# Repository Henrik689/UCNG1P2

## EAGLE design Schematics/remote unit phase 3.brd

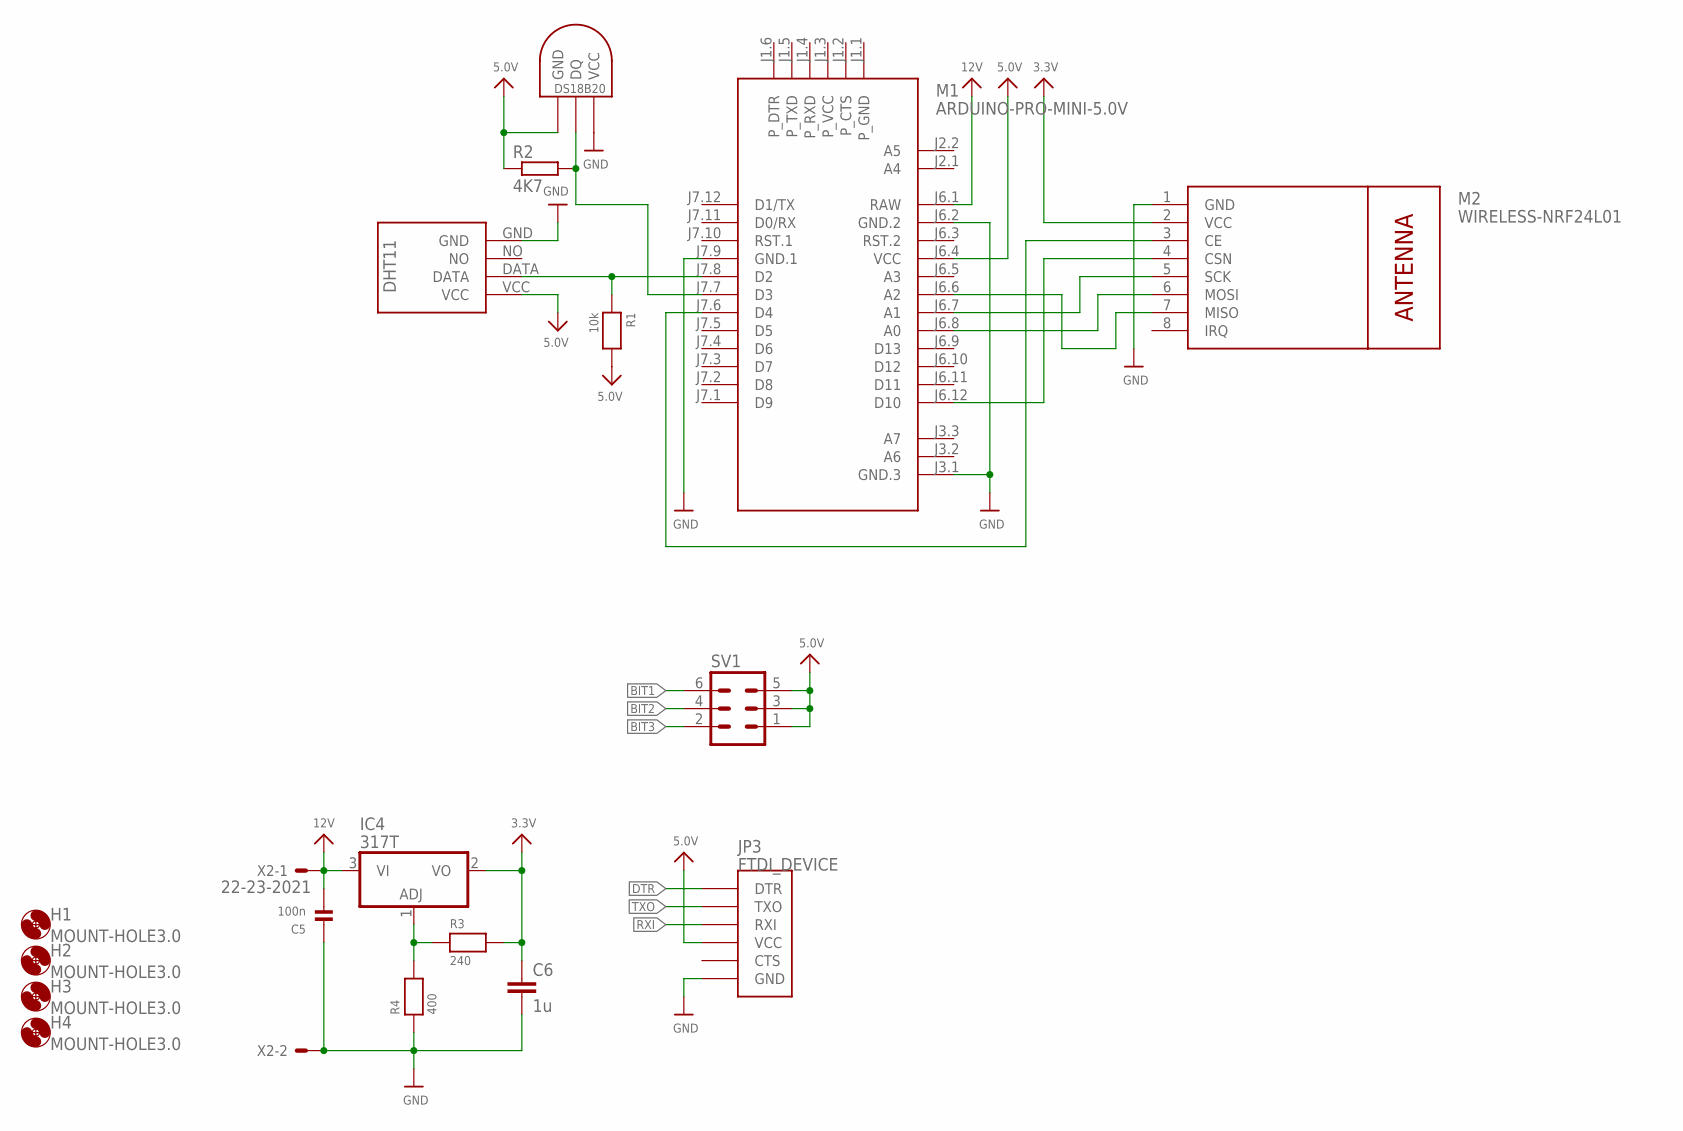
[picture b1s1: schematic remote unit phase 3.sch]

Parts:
C5: 100n; _0603
C6: 1u; C050-035X075
H1, H2, H3, H4: MOUNT-HOLE3.0; 3,0
IC4: 317T; TO220H
JP3: FTDI_DEVICE; FTDI_DEVICE_SIDE
M1: ARDUINO-PRO-MINI-5.0V; ARDUINO-PRO-MINI
M2: WIRELESS-NRF24L01
R1: 10k; _0603
R2: 4K7; 0204/5
R3: 240; _0603
R4: 400; _0603
SV1: MA03-2
U$6: DHT11
U$14: DS1820TO92; DS1820
X2: 22-23-2021

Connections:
3.3V: C6.1, IC4.2 (VO), M2.2 (VCC), R3.2
5.0V: JP3.P$4 (VCC), M1.J6.4 (VCC), R1.2, R2.1, SV1.1, SV1.3, SV1.5, U$6.VCC, U$14.GND
12V: C5.2, IC4.3 (VI), M1.J6.1 (RAW), X2.1
BIT1: SV1.6
BIT2: SV1.4
BIT3: SV1.2
CE: M1.J7.6 (D4), M2.3 (CE)
CSN: M1.J6.12 (D10), M2.4 (CSN)
DHT11: M1.J7.8 (D2), R1.1, U$6.DATA
DTR: JP3.P$1 (DTR)
GND: C5.1, C6.2, JP3.P$6 (GND), M1.J3.1 (GND.3), M1.J6.2 (GND.2), M1.J7.9 (GND.1), M2.1 (GND), R4.1, U$6.GND, U$14.VDD (VCC), X2.2
MISO: M1.J6.6 (A2), M2.7 (MISO)
MOSI: M1.J6.8 (A0), M2.6 (MOSI)
unnamed: IC4.1 (ADJ), R3.1, R4.2
RXI: JP3.P$3 (RXI)
SCK: M1.J6.7 (A1), M2.5 (SCK)
TEMP: M1.J7.7 (D3), R2.2, U$14.DQ
TXO: JP3.P$2 (TXO)

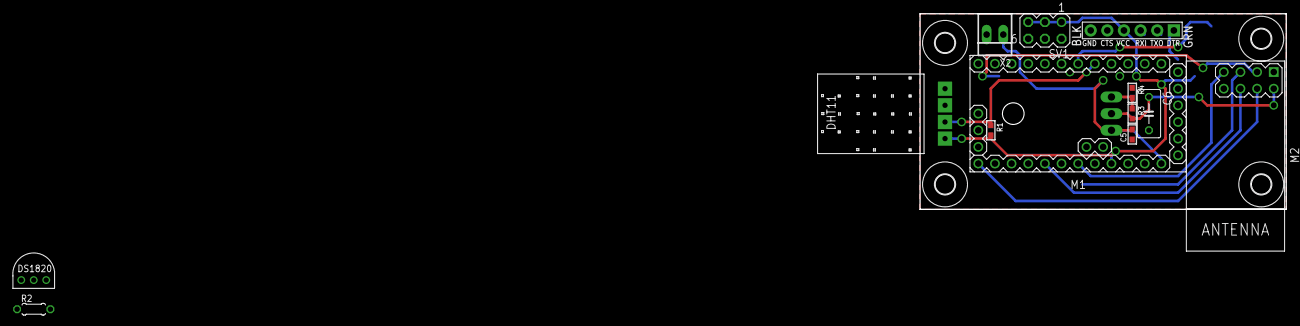
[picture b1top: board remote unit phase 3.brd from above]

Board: 2 copper layers, 55.9 x 29.8 mm, 18 parts (1 on the bottom side), 12 nets.

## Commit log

2016-01-04 added rapport for future editing
2016-01-04 Rod
    Har ændret enkelte ting introduktion
2016-01-04 Ændret forside til nyt projekt
2016-01-04 Ændringer i titlesheet og preface
2016-01-04 Ændringer i rapporten
    Rapporten er slavisk kørt igennem med ændringer
2016-01-04 tilføjet filer og ændret i master
    tilføjet sensor og accepttest
2016-01-04 ændring i master
2016-01-04 Removed ignored files
2016-01-04 sensor afsnit
    skrevet en smule på det
2016-01-04 Kravspecifikation
2016-01-04 ændret i sensor afsnit
2016-01-04 rettet kravspec
2016-01-04 sensor afsnit lavet tabel (ikke færdig)
2016-01-05 rettelser i kravsepc
2016-01-05 Introduktion til kravspec
2016-01-05 Kildehenvisning begyndt
2016-01-05 sensor afsnit
2016-01-05 tilføjet problemanalyse dokument
2016-01-05 hardware krav lavet
2016-01-05 TBD i hardware krav
2016-01-05 tilføjet 2 filer til problemanalyse
2016-01-05 Fixet tabel caption
2016-01-05 Enkelte stavefejl
2016-01-05 Billeder af fase 1-3
2016-01-05 indleding afsnit
2016-01-05 ændringer i master
2016-01-06 rettelse i hardware
2016-01-06 Hardware diagram indsat
2016-01-06 tilføjet krav til software afsnit
2016-01-06 Ændret i kravspec
2016-01-06 Software flowchart tilføjet
2016-01-06 Ændringer i software og master
2016-01-06 Intro til hardware samt fix af figure caption
2016-01-06 problemanalyse
2016-01-06 indledning redigeret
2016-01-06 fxnote test
2016-01-06 added fixme package
2016-01-07 FixMe notes tilføjet til alle sider
2016-01-07 tilføjet .lox og .nls til gitignore
2016-01-07 One Wire eksempel blibbiotek
2016-01-08 one wire filer
2016-01-11 tilføjet sensor afsnit
2016-01-11 Initimingfig
2016-01-11 ændring i sensor afsnit + tilføjet billeder
2016-01-11 Uploadet schematics
2016-01-11 Indsat subsection til schematic
2016-01-11 Schematics og billeder hertil
    Ikke helt færdig
2016-01-11 mikroprocessor startet
2016-01-12 litteraturliste
2016-01-12 ds18b20 tilføjet til litteraturliste
2016-01-12 software afsnit
2016-01-12 Fase1 software flowchart1
2016-01-12 mikroprocessor done
2016-01-12 mikroprocessor indsat billede
2016-01-12 rettelse i mikroprocessor
2016-01-12 Mikroprocessor_rettet
2016-01-13 rettelse af sensorafsnit, og sidste schematics
2016-01-13 Mikroprocessor_rettelse2
2016-01-13 microprocessor rettelse 3
2016-01-13 Rettelse af figurFase1software2
2016-01-13 hardware krav redigeret
2016-01-13 Rettelse af softwarestruktur
2016-01-13 Figur Fase1software2
2016-01-13 hardware introduktion lavet
2016-01-13 Onewire eksempel
2016-01-13 Software opdate
2016-01-13 Glossary ændret og hardware sensor påbegyndt
2016-01-13 Mikro update
2016-01-13 Problemanalysen update
2016-01-13 ds18b20 færdigt i hardware
2016-01-13 sensor redigeret i hardware
2016-01-13 Billeder til vandspild
2016-01-13 Tilføjet dht11 i hardware
2016-01-14 Figur update i PA
2016-01-14 Figur update PA
2016-01-14 Update PA
2016-01-14 rettet i sensor i hardware
2016-01-14 PA update
2016-01-14 flyttede videre udvikling over konklussion
2016-01-14 fxnote
2016-01-14 Update på indledningen
2016-01-14 Update indledning
2016-01-14 enkelte rettelser i software
2016-01-14 indsat tabel og pris i hardware samt redigeret i sensor tabel
2016-01-14 tal rettet i hardware tabel
2016-01-14 flyttede videre udvikling igen
2016-01-14 har fikset flowchart for fase 2
2016-01-15 tilføjet labet til fase 1 flowchart
2016-01-15 tilføjet label til fase 1 flowchart
2016-01-15 minor settings change and more work on rapport
2016-01-16 har fået skrevet om fase 2 og websiden samt ethernet
2016-01-16 hard- og software pris og tabel lavet
2016-01-16 BOM fjernet og redigeret pris hard- og software
2016-01-16 Fået skrevet det meste af afsnittet færdigt
    mangler at færdiggøre mesh afsnittet
2016-01-17 PA klar til gennemlæsning
2016-01-17 fortsat arbejde på videre udvikling
2016-01-17 Arkitektur og software beskrivelse
2016-01-18 sensor+one wire afsnit
2016-01-18 added .lox to git ignore
2016-01-18 removed accepttest
2016-01-18 opdateret grafer til vandspild
2016-01-18 konklusion
2016-01-18 Pris færdig - soft- og hardware
2016-01-18 Begrundelse for DHT11
2016-01-18 master + konklusion + perspektivering
2016-01-18 Konklussion + perspektivering
2016-01-18 fxnotes
2016-01-18 master
2016-01-18 master Porsborg har mærkelige fejl
2016-01-19 startet på rette processen
2016-01-19 master tidsplan
2016-01-20 Rettelser i mange filer, inkl en figur og .lox
2016-01-20 Forkortelser og små rettelser
2016-01-20 konklusion
    skrevet helt om
2016-01-20 Små rettelser
2016-01-20 har fikset listen med forkortelser
2016-01-20 Videreudvikling rettelser
2016-01-20 færdig med at tilføje forkortelser til glossary listen
2016-01-20 rettelser og milesten
2016-01-20 kravspek og hardware spek
2016-01-20 master - slettet user guide
2016-01-20 rettelser i software
2016-01-20 Gennemlæsning af hardware
2016-01-20 software DONE
2016-01-20 Software DONE igen....
2016-01-20 master ændret
2016-01-20 Oversat lister til dansk
2016-01-20 Mikroprocesser
2016-01-21 Afsluttende rettelser
2016-01-21 ændrede glossary til ordliste
2016-01-21 problemstilling
2016-01-21 hardwarestruktur
2016-01-21 hardware struktur billede
2016-01-21 vandspild grafer
2016-01-21 hardware struktur
2016-01-21 rettelser i billede
2016-01-21 Rettelser i alt
2016-01-21 billeder
2016-01-21 forside
2016-01-21 added arduino code LSTlistings
2016-01-21 rettelse af billedplacering
2016-01-21 Software appendiks
2016-01-21 opdateret billede til videre udvikling
2016-01-21 videreudviklings billede
2016-01-21 billede placering
2016-01-21 billede af terminaloutput
2016-01-21 billede placering og størrelser
2016-01-21 opdateret init timing billede
2016-01-21 videre udvikling
2016-01-21 Terminaloutput
2016-01-21 sidste rettelser

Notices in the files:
parts and their libraries:
SparkFun-Connectors: Licensing: Creative Commons ShareAlike 4.0 International - https://creativecommons.org/licenses/by-sa/4.0
diy-modules: Released under the Creative Commons Attribution 4.0 International License: http://creativecommons.org/licenses/by/4.0
